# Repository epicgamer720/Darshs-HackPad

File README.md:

# Darshs-HackPad

BOM :

1x XIAO RP2040

9x MX-Style switches (traslucent ones please)

9x SK8612-e MINI led 

1x Rotary Encoder EC11

1x 0.91 inch OLED display

9x Through-hole 1N4148 Diodes

4x M3x16mm screws

4x M3 heatset inserts

mabye a few extra leds and diodes just incase please and mabye one or 2 switches to fidget with

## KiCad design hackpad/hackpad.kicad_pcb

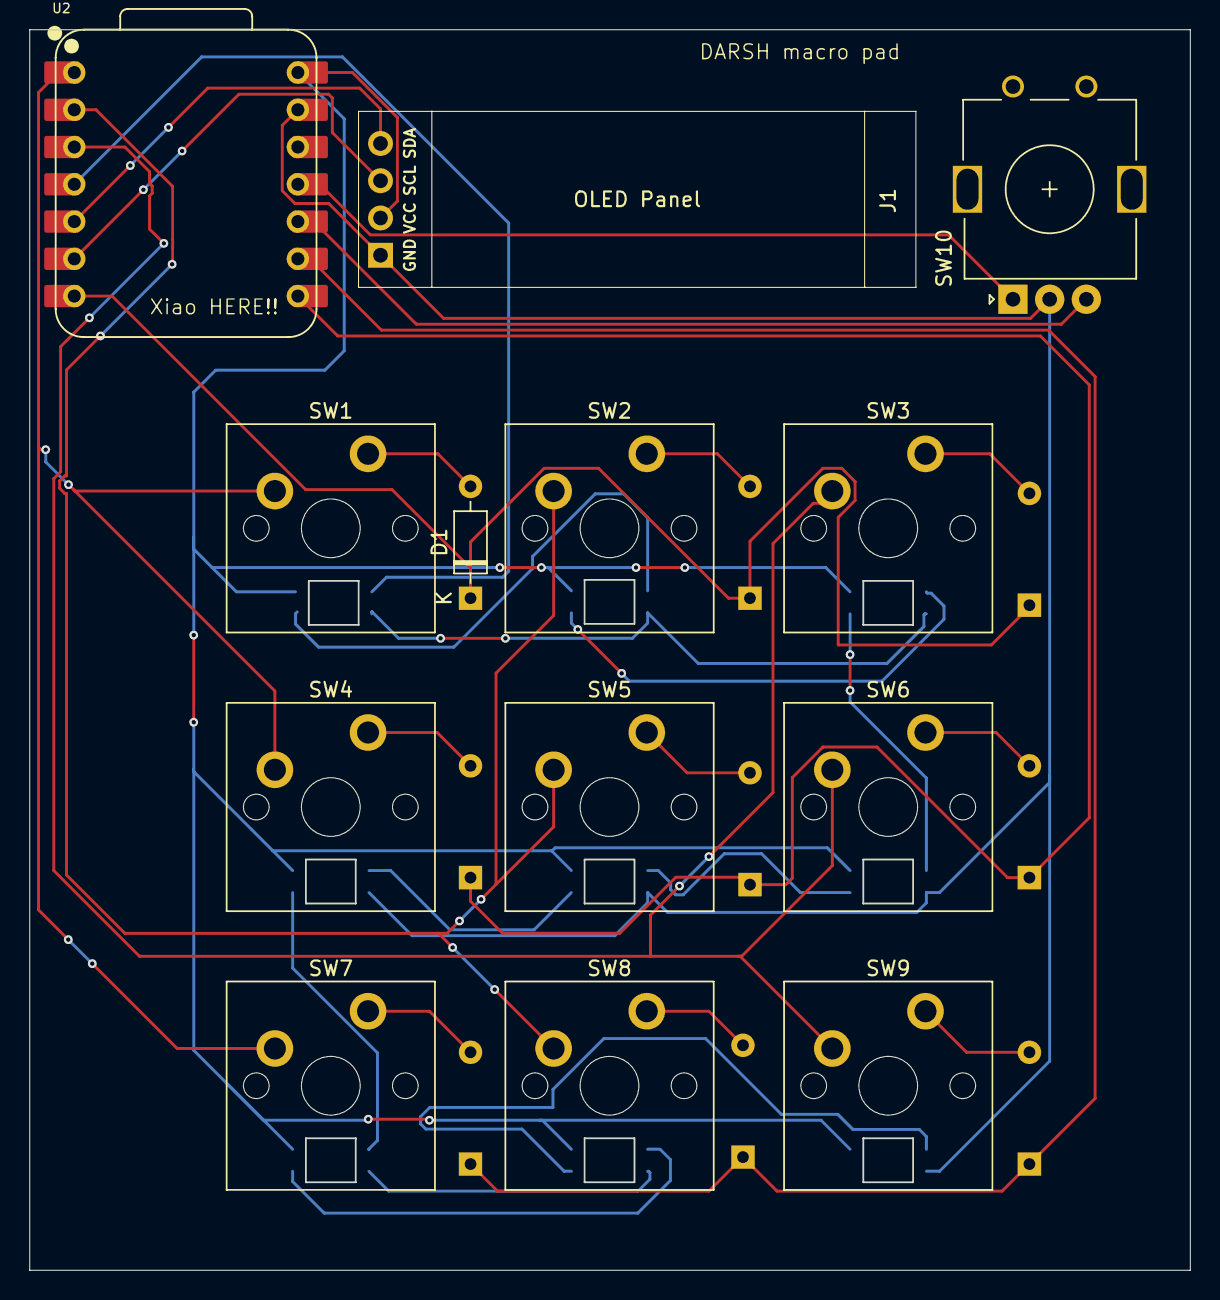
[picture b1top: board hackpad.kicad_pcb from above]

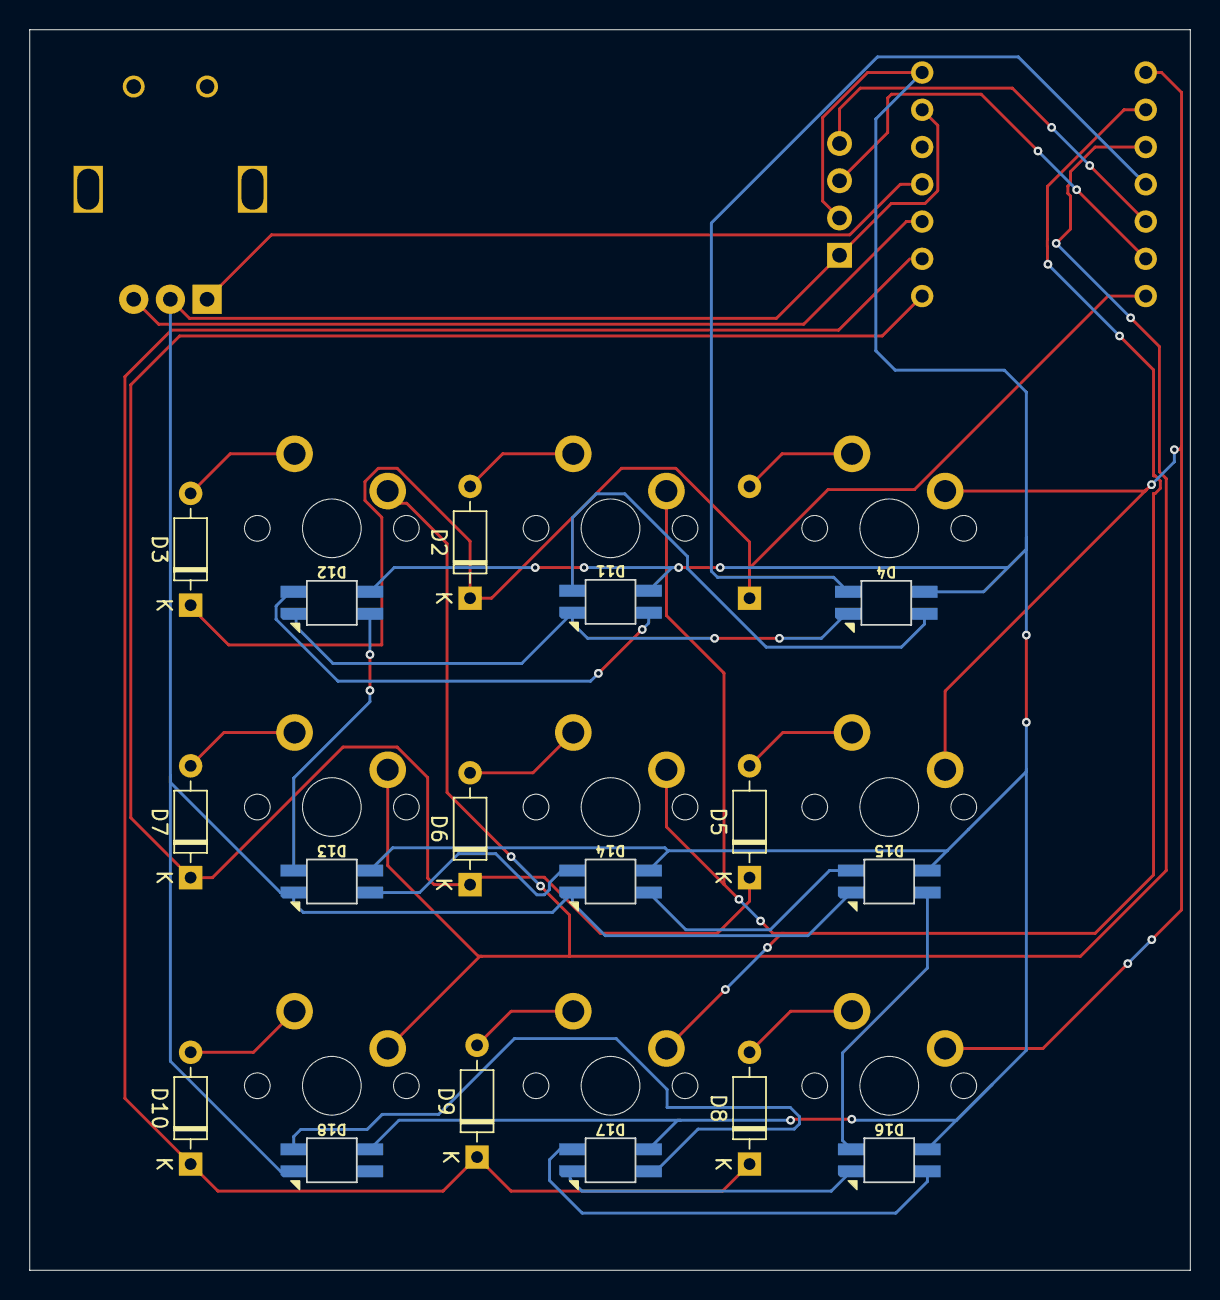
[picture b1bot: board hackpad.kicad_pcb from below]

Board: 2 copper layers, 79.0 x 84.5 mm, 30 parts (17 on the bottom side), 30 nets.

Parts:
D1, D2, D3, D5, D6, D7, D8, D9, D10: 1N4148; D_DO-35_SOD27_P7.62mm_Horizontal
D4, D11, D12, D13, D14, D15, D16, D17, D18: SK6812MINI; SK6812MINI-E
J1: OLED_128x32; SSD1306-0.91-OLED-4pin-128x32
SW1, SW2, SW3, SW4, SW5, SW6, SW7, SW8, SW9: SW_Push; MX_PCB_1.00u
SW10: RotaryEncoder_Switch; RotaryEncoder_Alps_EC11E_Vertical_H20mm
U2: XIAO-RP2040-DIP

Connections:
+5V: D4.4 (VDD), D11.4 (VDD), D12.4 (VDD), D13.4 (VDD), D14.4 (VDD), D15.4 (VDD), D16.4 (VDD), D17.4 (VDD), D18.4 (VDD), J1.2 (VCC), U2.14 (VBUS)
Column 0: SW1.1, SW4.1, SW7.1, U2.1 (GPIO26/ADC0/A0)
Column 1: SW2.1, SW5.1, SW8.1, U2.2 (GPIO27/ADC1/A1)
Column 2: SW3.1, SW6.1, SW9.1, U2.3 (GPIO28/ADC2/A2)
ENC11 A: SW10.A, U2.11 (GPIO3/MOSI)
ENC11 B: SW10.B, U2.10 (GPIO4/MISO)
GND: D4.2 (VSS), D11.2 (VSS), D12.2 (VSS), D13.2 (VSS), D14.2 (VSS), D15.2 (VSS), D16.2 (VSS), D17.2 (VSS), D18.2 (VSS), J1.1 (GND), SW10.C, U2.13 (GND)
unnamed: D1.2 (A), SW1.2
unnamed: D2.2 (A), SW2.2
unnamed: D3.2 (A), SW3.2
unnamed: D5.2 (A), SW4.2
unnamed: D6.2 (A), SW5.2
unnamed: D7.2 (A), SW6.2
unnamed: D8.2 (A), SW7.2
unnamed: D9.2 (A), SW8.2
unnamed: D10.2 (A), SW9.2
unnamed: D4.1 (DOUT), D11.3 (DIN)
unnamed: D11.1 (DOUT), D12.3 (DIN)
unnamed: D12.1 (DOUT), D13.3 (DIN)
unnamed: D13.1 (DOUT), D14.3 (DIN)
unnamed: D14.1 (DOUT), D15.3 (DIN)
unnamed: D15.1 (DOUT), D16.3 (DIN)
unnamed: D16.1 (DOUT), D17.3 (DIN)
unnamed: D17.1 (DOUT), D18.3 (DIN)
RGB: D4.3 (DIN), U2.4 (GPIO29/ADC3/A3)
Row 0: D1.1 (K), D2.1 (K), D3.1 (K), U2.7 (GPIO0/TX)
Row 1: D5.1 (K), D6.1 (K), D7.1 (K), U2.8 (GPIO1/RX)
Row 2: D8.1 (K), D9.1 (K), D10.1 (K), U2.9 (GPIO2/SCK)
SCL OLED: J1.3 (SCL), U2.6 (GPIO7/SCL)
SDA OLED: J1.4 (SDA), U2.5 (GPIO6/SDA)

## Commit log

2025-12-26 Expand README with BOM and project images
    Added a detailed BOM and images for the project.
2025-12-26 Update BOM with extra components and notes
    Added additional components and notes to the BOM section.
2025-12-26 Add more images to README
    Added additional images to the README for better reference.
